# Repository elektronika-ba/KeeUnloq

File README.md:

# KeeUnloq
Tool for playing with Microchip KeeLoq technology.

# Status
Under development. More information will be available on www.elektronika.ba

Read the doc @ [Documentation](doc/KeeUnloq_fw1.0.docx)

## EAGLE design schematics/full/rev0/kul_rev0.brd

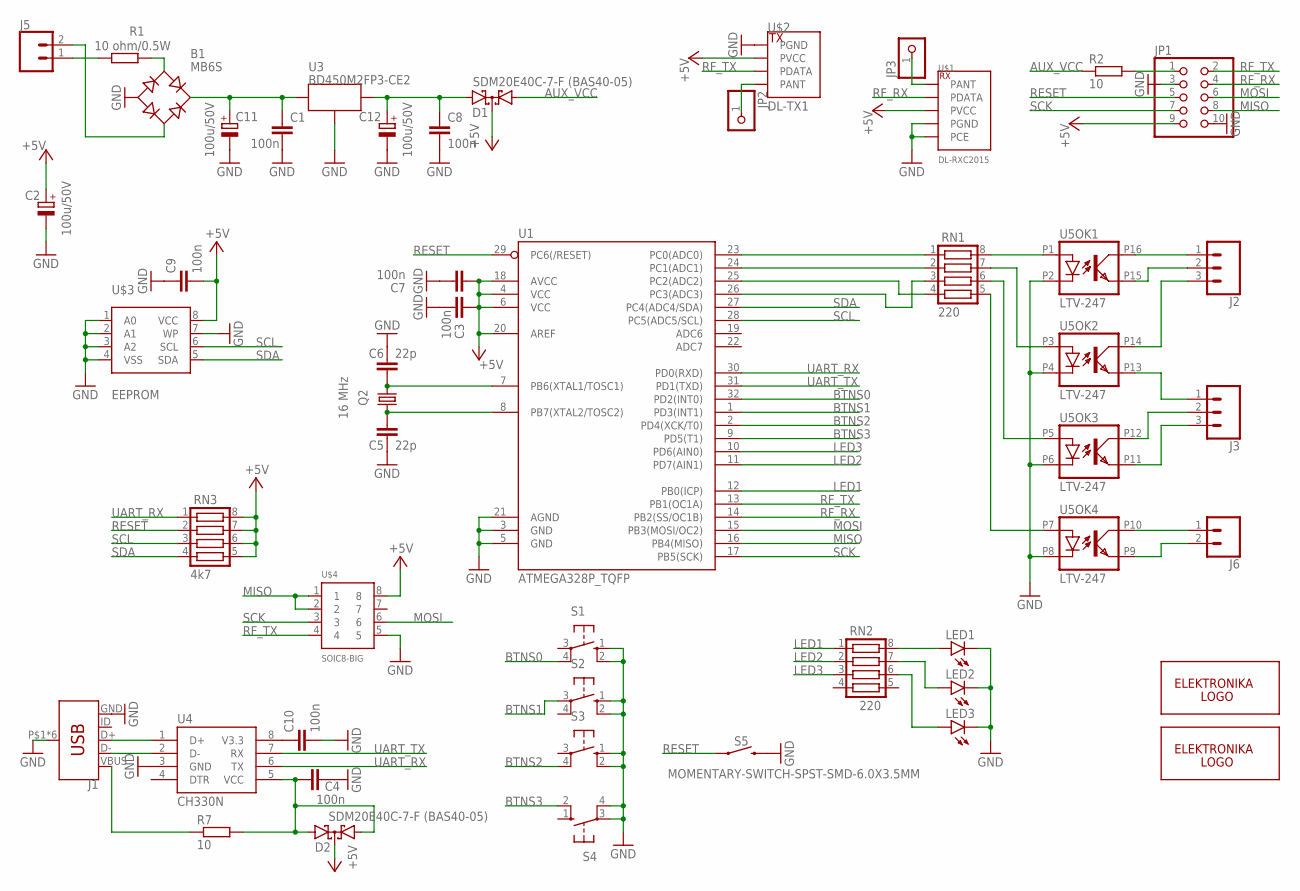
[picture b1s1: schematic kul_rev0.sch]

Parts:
B1: MB6S; SOIC-4
C1, C3, C4, C7, C8, C9, C10: 100n; C0603
C2, C11, C12: 100u/50V; E5-6
C5, C6: 22p; C0603
D1, D2: SDM20E40C-7-F (BAS40-05); SOT23
J1: USB_MICRO-BLCSC; C40951_USB
J2, J3: CONN_03SCREW_LOCK; SCREWTERMINAL-3.5MM-3_LOCK.007S
J5, J6: CONN_023.5MM; SCREWTERMINAL-3.5MM-2
JP1: PINHD-2X5; 2X05
JP2, JP3: PINHD-1X1; 1X01
LED1, LED2, LED3: LEDCHIP-LED0805; CHIP-LED0805
Q2: 16 MHz; 3.2X2.5_KX-7
R1: 10 ohm/0.5W; R0805
R2, R7: 10; R0603
RN1, RN2: 220; CTS742C083
RN3: 4k7; CTS742C083
S1, S2, S3, S4: 10-XX; B3F-10XX
S5: MOMENTARY-SWITCH-SPST-SMD-6.0X3.5MM; TACTILE_SWITCH_SMD_6.0X3.5MM
U1: ATMEGA328P_TQFP; TQFP32-08
U3: BD450M2FP3-CE2; C308597_LDO
U4: CH330N; SOIC8
U5: LTV-247; SOP-16_4.4MM
U$1: DL-RXC2015
U$2: DL-TX1
U$3: EEPROM; SOIC8
U$4: SOIC8-BIG; SOIC8_BIG
U$5: ELEKTRONIKA_BA_ELEBA_LOGO-121; ELEKTRONIKA_BA_ELEBALOGO_ELEBALOGO_B_121
U$6: ELEKTRONIKA_BA_ELEBA_LOGO; ELEKTRONIKA_BA_ELEBALOGO_ELEBALOGO_B_122

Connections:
+5V: C2.+, C3.2, C7.2, C9.2, D1.3 (C), D2.3 (C), JP1.9, RN3.5, RN3.6, RN3.7, RN3.8, U1.4 (VCC), U1.6 (VCC), U1.18 (AVCC), U1.20 (AREF), U$1.PVCC, U$2.PVDD (PVCC), U$3.8 (VCC), U$4.8
AUX_VCC: D1.1 (A1), R2.1
BTNS0: S1.4 (P1), U1.32 (PD2(INT0))
BTNS1: S2.3, U1.1 (PD3(INT1))
BTNS2: S3.4 (P1), U1.2 (PD4(XCK/T0))
BTNS3: S4.2 (S1), U1.9 (PD5(T1))
GND: B1.-, C1.2, C2.-, C3.1, C4.2, C5.2, C6.1, C7.1, C8.2, C9.1, C10.2, C11.-, C12.-, J1.GND, J1.P$1 (SHIELD), J1.P$2 (SHIELD), J1.P$3 (SHIELD), J1.P$4 (SHIELD), J1.SHIELD1 (SHIELD), J1.SHIELD2 (SHIELD), JP1.3, JP1.10, LED1.C, LED2.C, LED3.C, S1.1 (S), S1.2 (S1), S2.1 (S), S2.2 (S1), S3.1 (S), S3.2 (S1), S4.3, S4.4 (P1), S5.2, U1.3 (GND), U1.5 (GND), U1.21 (AGND), U3.PGND1 (PGND), U3.PGND2 (PGND), U4.3 (GND), U5.P2 (C), U5.P4 (C), U5.P6 (C), U5.P8 (C), U$1.PCE, U$1.PGND1 (PGND), U$1.PGND2 (PGND), U$2.PGND, U$3.1 (A0), U$3.2 (A1), U$3.3 (A2), U$3.4 (VSS), U$3.7 (WP), U$4.5
LED1: RN2.1, U1.12 (PB0(ICP))
LED2: RN2.2, U1.11 (PD7(AIN1))
LED3: RN2.3, U1.10 (PD6(AIN0))
MISO: JP1.8, U1.16 (PB4(MISO)), U$4.1, U$4.2
MOSI: JP1.6, U1.15 (PB3(MOSI/OC2)), U$4.6
unnamed: RN1.8, U5.P1 (A)
unnamed: RN1.7, U5.P3 (A)
unnamed: RN1.6, U5.P5 (A)
unnamed: RN1.5, U5.P7 (A)
unnamed: RN1.4, U1.25 (PC2(ADC2))
unnamed: RN1.3, U1.26 (PC3(ADC3))
unnamed: J1.D+, U4.1 (D+)
unnamed: B1.~1 (AC1), R1.1
unnamed: B1.~2 (AC2), J5.2
unnamed: B1.+, C1.1, C11.+, U3.PIN
unnamed: C8.1, C12.+, D1.2 (A2), U3.POUT
unnamed: J5.1, R1.2
unnamed: J1.D-, U4.2 (D-)
unnamed: J1.VBUS, R7.1
unnamed: C4.1, D2.1 (A1), D2.2 (A2), R7.2, U4.5 (VCC)
unnamed: C10.1, U4.8 (V3.3)
unnamed: J2.1, U5.P16 (COL)
unnamed: J2.2, U5.P15 (EMIT)
unnamed: J2.3, U5.P14 (COL)
unnamed: J3.1, U5.P13 (EMIT)
unnamed: J3.2, U5.P12 (COL)
unnamed: J3.3, U5.P11 (EMIT)
unnamed: J6.1, U5.P10 (COL)
unnamed: J6.2, U5.P9 (EMIT)
unnamed: RN1.1, U1.23 (PC0(ADC0))
unnamed: RN1.2, U1.24 (PC1(ADC1))
unnamed: JP2.1, U$2.PANT
unnamed: JP3.1, U$1.PANT
unnamed: LED1.A, RN2.8
unnamed: LED2.A, RN2.7
unnamed: LED3.A, RN2.6
unnamed: JP1.1, R2.2
OSC1: C6.2, Q2.3 (2), U1.7 (PB6(XTAL1/TOSC1))
OSC2: C5.1, Q2.1, U1.8 (PB7(XTAL2/TOSC2))
RESET: JP1.5, RN3.2, S5.1, U1.29 (PC6(/RESET))
RF_RX: JP1.4, U1.14 (PB2(SS/OC1B)), U$1.PDATA
RF_TX: JP1.2, U1.13 (PB1(OC1A)), U$2.PDATA, U$4.4
SCK: JP1.7, U1.17 (PB5(SCK)), U$4.3
SCL: RN3.3, U1.28 (PC5(ADC5/SCL)), U$3.6 (SCL)
SDA: RN3.4, U1.27 (PC4(ADC4/SDA)), U$3.5 (SDA)
UART_RX: RN3.1, U1.30 (PD0(RXD)), U4.6 (TX)
UART_TX: U1.31 (PD1(TXD)), U4.7 (RX)

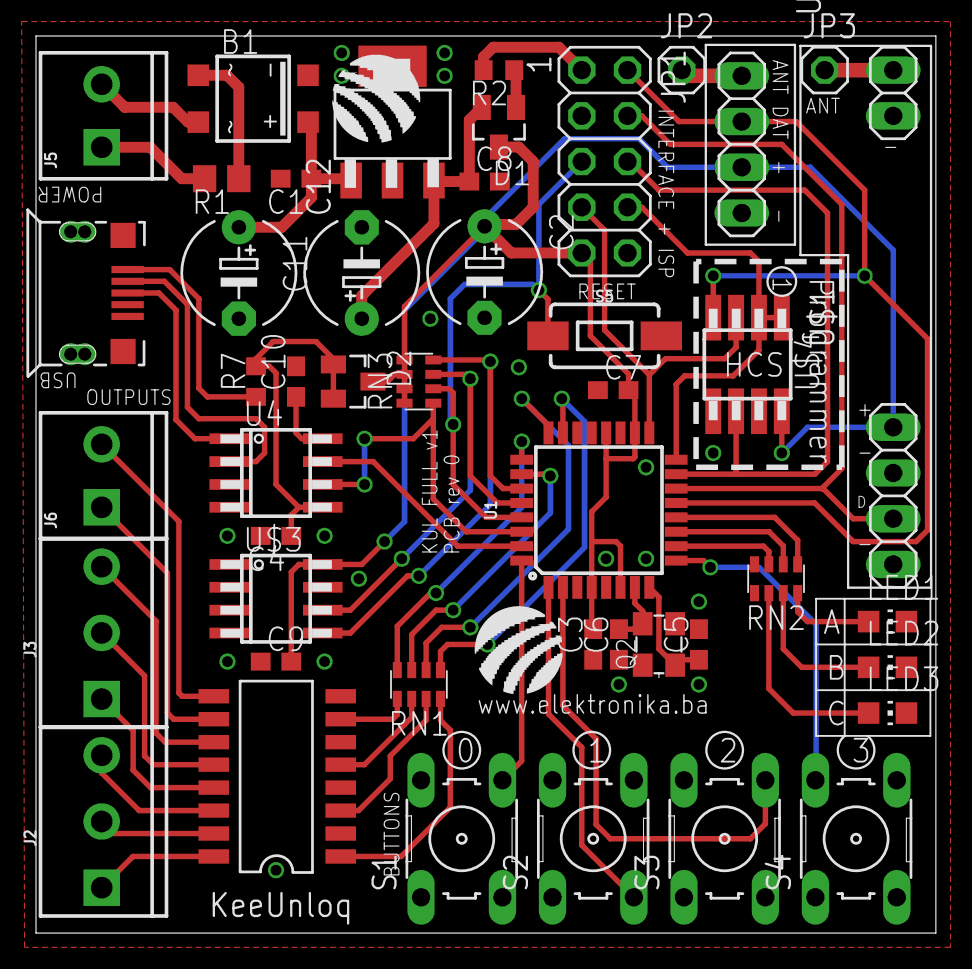
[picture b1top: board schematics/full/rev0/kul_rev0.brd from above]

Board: 2 copper layers, 50.0 x 49.8 mm, 48 parts (1 on the bottom side), 54 nets.

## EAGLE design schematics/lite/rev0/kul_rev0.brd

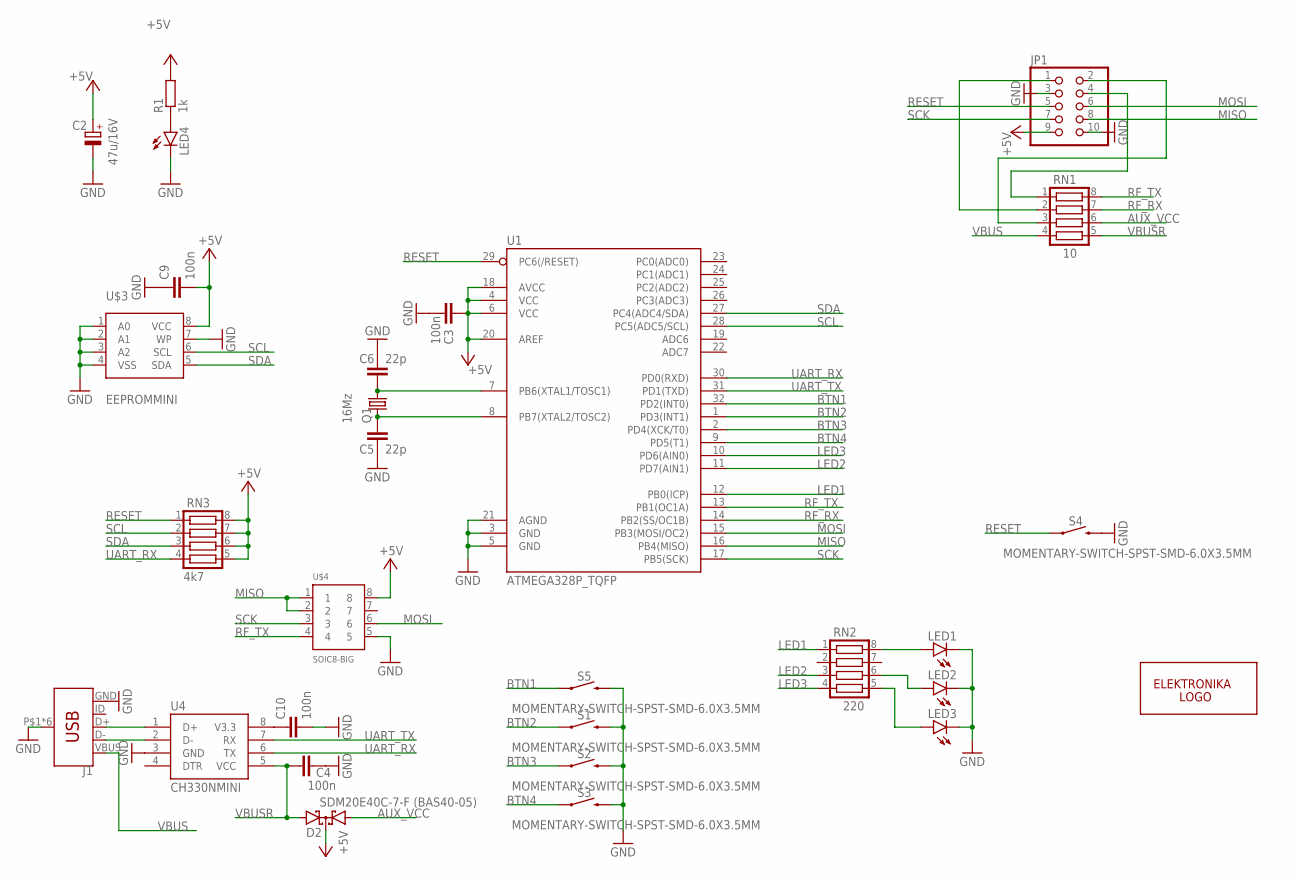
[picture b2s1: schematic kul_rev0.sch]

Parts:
C2: 47u/16V; CT6032
C3, C4, C9, C10: 100n; C0603
C5, C6: 22p; C0603
D2: SDM20E40C-7-F (BAS40-05); SOT23
J1: USB_MICRO-BLCSC; C40951_USB
JP1: PINHD-2X5/90; 2X05/90
LED1, LED2, LED3, LED4: LEDCHIP-LED0805; CHIP-LED0805
Q1: 16Mz; 3.2X2.5_KX-7
R1: 1k; R0603
RN1: 10; CTS742C083
RN2: 220; CTS742C083
RN3: 4k7; CTS742C083
S1, S2, S3, S4, S5: MOMENTARY-SWITCH-SPST-SMD-6.0X3.5MM; TACTILE_SWITCH_SMD_6.0X3.5MM
U1: ATMEGA328P_TQFP; TQFP32-08
U4: CH330NMINI; SOIC8_MINI
U$3: EEPROMMINI; SOIC8_MINI
U$4: SOIC8-BIG; SOIC8_BIG
U$6: ELEKTRONIKA_BA_ELEBA_LOGO; ELEKTRONIKA_BA_ELEBALOGO_ELEBALOGO_B_122

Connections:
+5V: C2.+, C3.2, C9.2, D2.3 (C), JP1.9, R1.2, RN3.5, RN3.6, RN3.7, RN3.8, U1.4 (VCC), U1.6 (VCC), U1.18 (AVCC), U1.20 (AREF), U$3.8 (VCC), U$4.8
AUX_VCC: D2.1 (A1), RN1.6
BTN1: S5.1, U1.32 (PD2(INT0))
BTN2: S1.1, U1.1 (PD3(INT1))
BTN3: S2.1, U1.2 (PD4(XCK/T0))
BTN4: S3.1, U1.9 (PD5(T1))
GND: C2.-, C3.1, C4.2, C5.2, C6.1, C9.1, C10.2, J1.GND, J1.P$1 (SHIELD), J1.P$2 (SHIELD), J1.P$3 (SHIELD), J1.P$4 (SHIELD), J1.SHIELD1 (SHIELD), J1.SHIELD2 (SHIELD), JP1.3, JP1.10, LED1.C, LED2.C, LED3.C, LED4.C, S1.2, S2.2, S3.2, S4.2, S5.2, U1.3 (GND), U1.5 (GND), U1.21 (AGND), U4.3 (GND), U$3.1 (A0), U$3.2 (A1), U$3.3 (A2), U$3.4 (VSS), U$3.7 (WP), U$4.5
LED1: RN2.1, U1.12 (PB0(ICP))
LED2: RN2.3, U1.11 (PD7(AIN1))
LED3: RN2.4, U1.10 (PD6(AIN0))
MISO: JP1.8, U1.16 (PB4(MISO)), U$4.1, U$4.2
MOSI: JP1.6, U1.15 (PB3(MOSI/OC2)), U$4.6
unnamed: JP1.2, RN1.3
unnamed: JP1.4, RN1.1
unnamed: LED2.A, RN2.6
unnamed: LED1.A, RN2.8
unnamed: LED4.A, R1.1
unnamed: J1.D+, U4.1 (D+)
unnamed: J1.D-, U4.2 (D-)
unnamed: C10.1, U4.8 (V3.3)
unnamed: LED3.A, RN2.5
unnamed: JP1.1, RN1.2
OSC1: C6.2, Q1.3 (2), U1.7 (PB6(XTAL1/TOSC1))
OSC2: C5.1, Q1.1, U1.8 (PB7(XTAL2/TOSC2))
RESET: JP1.5, RN3.1, S4.1, U1.29 (PC6(/RESET))
RF_RX: RN1.7, U1.14 (PB2(SS/OC1B))
RF_TX: RN1.8, U1.13 (PB1(OC1A)), U$4.4
SCK: JP1.7, U1.17 (PB5(SCK)), U$4.3
SCL: RN3.2, U1.28 (PC5(ADC5/SCL)), U$3.6 (SCL)
SDA: RN3.3, U1.27 (PC4(ADC4/SDA)), U$3.5 (SDA)
UART_RX: RN3.4, U1.30 (PD0(RXD)), U4.6 (TX)
UART_TX: U1.31 (PD1(TXD)), U4.7 (RX)
VBUS: J1.VBUS, RN1.4
VBUSR: C4.1, D2.2 (A2), RN1.5, U4.5 (VCC)

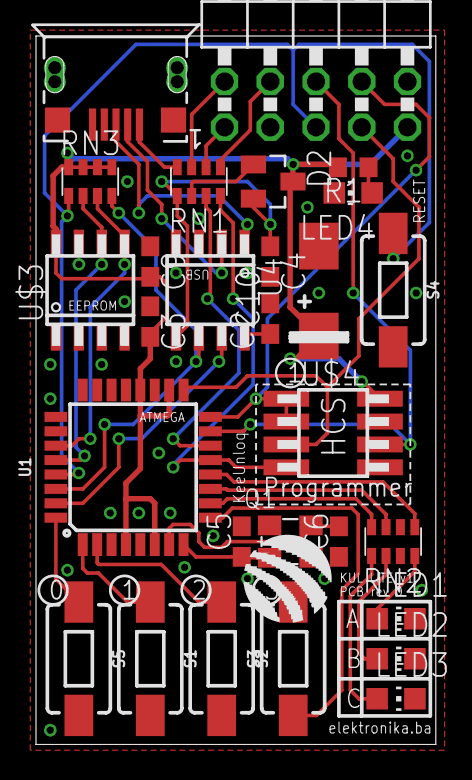
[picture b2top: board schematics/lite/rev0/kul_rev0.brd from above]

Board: 2 copper layers, 22.2 x 39.4 mm, 29 parts (1 on the bottom side), 34 nets.

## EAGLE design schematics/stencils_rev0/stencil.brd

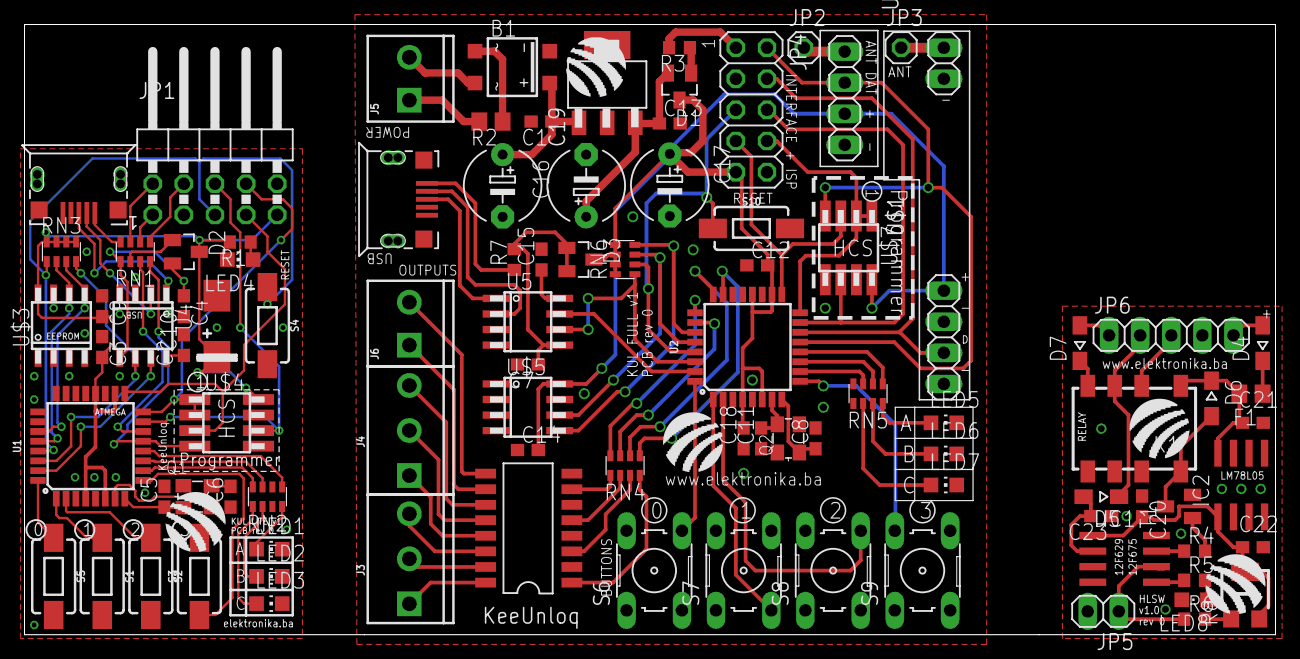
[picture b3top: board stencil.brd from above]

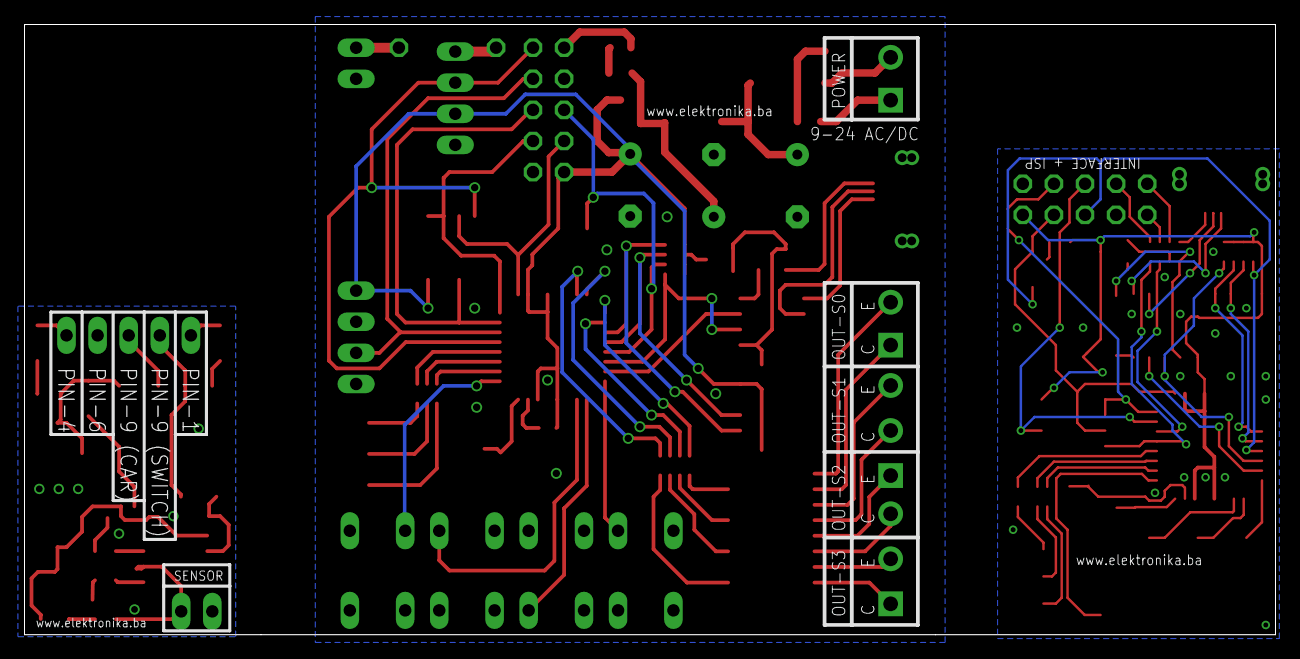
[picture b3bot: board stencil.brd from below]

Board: 2 copper layers, 102.2 x 49.8 mm, 99 parts (3 on the bottom side), 105 nets.

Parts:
B1: MB6S; SOIC-4
C1, C3, C4, C7, C9, C10, C12, C13, C14, C15, C18, C20, C23: 100n; C0603
C2: 47u/16V; CT6032
C5, C6, C8, C11: 22p; C0603
C16, C17, C19: 100u/50V; E5-6
C21: 470n; C0603
C22: 330n; C0603
D1, D2, D3: SDM20E40C-7-F (BAS40-05); SOT23
D4, D5, D6, D7: 1N4148; SOD323-W
F1: PTC 0.1A 15V; R0805
IC1: PIC12F675SN; SO-08
IC2: 78L05SMD; SO08
J1, J2: C40951_USB
J3, J4: SCREWTERMINAL-3.5MM-3_LOCK.007S
J5, J6: SCREWTERMINAL-3.5MM-2
JP1: 2X05/90
JP2, JP3: 1X01
JP4: 2X05
JP5: 1X02
JP6: 1X05
K1: G6K-2F-Y
LED1, LED2, LED3, LED4, LED5, LED6, LED7: CHIP-LED0805
LED8: RED; CHIPLED_0805
Q1: 16Mz; 3.2X2.5_KX-7
Q2: 16 MHz; 3.2X2.5_KX-7
R1, R5, R6: 1k; R0603
R2: 22; R0805
R3, R7: 10; R0603
R4: 2k2; R0603
R8: 15k; RTRIMCVR42A
RN1: 10; CTS742C083
RN2, RN4, RN5: 220; CTS742C083
RN3, RN6: 4k7; CTS742C083
S1, S2, S3, S4, S5, S10: MOMENTARY-SWITCH-SPST-SMD-6.0X3.5MM; TACTILE_SWITCH_SMD_6.0X3.5MM
S6, S7, S8, S9: B3F-10XX
T1: BC546; SOT23-BEC
U1, U2: ATMEGA328P_TQFP; TQFP32-08
U3: BD450M2FP3-CE2; C308597_LDO
U4: CH330NMINI; SOIC8_MINI
U5: CH330N; SOIC8
U6: LTV-247; SOP-16_4.4MM
U$1: DL-RXC2015
U$2: DL-TX1
U$3: EEPROMMINI; SOIC8_MINI
U$4, U$7: SOIC8-BIG; SOIC8_BIG
U$5: EEPROM; SOIC8
U$6, U$9, U$10: ELEKTRONIKA_BA_ELEBA_LOGO; ELEKTRONIKA_BA_ELEBALOGO_ELEBALOGO_B_122
U$8, U$11: ELEKTRONIKA_BA_ELEBA_LOGO-121; ELEKTRONIKA_BA_ELEBALOGO_ELEBALOGO_B_121

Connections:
1-PIN: D7.A, JP6.1
4-PIN: D4.A, JP6.5
9-CAR: JP6.3, K1.2
9-HLSW: D5.C, JP6.2, K1.3
!ENAB: C23.2, D5.A, IC1.2
+5V: C2.+, C3.2, C9.2, D2.3, JP1.9, R1.2, RN3.5, RN3.6, RN3.7, RN3.8, U1.4, U1.6, U1.18, U1.20, U$3.8, U$4.8
+5V1: C12.2, C14.2, C17.+, C18.2, D1.3, D3.3, JP4.9, RN6.5, RN6.6, RN6.7, RN6.8, U2.4, U2.6, U2.18, U2.20, U$1.PVCC, U$2.PVDD, U$5.8, U$7.8
+5V2: C20.2, C22.1, IC1.1, IC2.1, R8.2, R8.3
+12V: C21.1, D6.C, F1.2, IC2.8, K1.1
AUX_VCC: D2.1, RN1.6
AUX_VCC1: D1.1, R3.1
BTN1: S5.1, U1.32
BTN2: S1.1, U1.1
BTN3: S2.1, U1.2
BTN4: S3.1, U1.9
BTN5: S6.4, U2.32
BTN6: S7.3, U2.1
BTN7: S8.4, U2.2
BTN8: S9.2, U2.9
GND: C2.-, C3.1, C4.2, C5.2, C6.1, C9.1, C10.2, J1.GND, J1.P$1, J1.P$2, J1.P$3, J1.P$4, J1.SHIELD1, J1.SHIELD2, JP1.3, JP1.10, LED1.C, LED2.C, LED3.C, LED4.C, S1.2, S2.2, S3.2, S4.2, S5.2, U1.3, U1.5, U1.21, U4.3, U$3.1, U$3.2, U$3.3, U$3.4, U$3.7, U$4.5
GND1: B1.-, C1.2, C7.2, C8.2, C11.1, C12.1, C13.2, C14.1, C15.2, C16.-, C17.-, C18.1, C19.-, J2.GND, J2.P$1, J2.P$2, J2.P$3, J2.P$4, J2.SHIELD1, J2.SHIELD2, JP4.3, JP4.10, LED5.C, LED6.C, LED7.C, S6.1, S6.2, S7.1, S7.2, S8.1, S8.2, S9.3, S9.4, S10.2, U2.3, U2.5, U2.21, U3.PGND1, U3.PGND2, U5.3, U6.P2, U6.P4, U6.P6, U6.P8, U$1.PCE, U$1.PGND1, U$1.PGND2, U$2.PGND, U$5.1, U$5.2, U$5.3, U$5.4, U$5.7, U$7.5
GND2: C20.1, C21.2, C22.2, C23.1, IC1.8, IC2.2, IC2.3, IC2.6, IC2.7, JP5.2, JP6.4, LED8.C, T1.E
LED1: RN2.1, U1.12
LED2: RN2.3, U1.11
LED3: RN2.4, U1.10
LED4: RN5.1, U2.12
LED5: RN5.2, U2.11
LED6: RN5.3, U2.10
MISO: JP1.8, U1.16, U$4.1, U$4.2
MISO1: JP4.8, U2.16, U$7.1, U$7.2
MOSI: JP1.6, U1.15, U$4.6
MOSI1: JP4.6, U2.15, U$7.6
unnamed: JP1.2, RN1.3
unnamed: JP1.4, RN1.1
unnamed: LED2.A, RN2.6
unnamed: LED1.A, RN2.8
unnamed: LED4.A, R1.1
unnamed: RN4.8, U6.P1
unnamed: RN4.7, U6.P3
unnamed: J1.D+, U4.1
unnamed: RN4.6, U6.P5
unnamed: RN4.5, U6.P7
unnamed: B1.~1, R2.1
unnamed: B1.~2, J5.2
unnamed: B1.+, C1.1, C16.+, U3.PIN
unnamed: J1.D-, U4.2
unnamed: C13.1, C19.+, D1.2, U3.POUT
unnamed: J2.D+, U5.1
unnamed: C10.1, U4.8
unnamed: J2.D-, U5.2
unnamed: J2.VBUS, R7.1
unnamed: C7.1, D3.1, D3.2, R7.2, U5.5
unnamed: C15.1, U5.8
unnamed: J3.1, U6.P16
unnamed: J3.2, U6.P15
unnamed: J3.3, U6.P14
unnamed: J4.1, U6.P13
unnamed: J4.2, U6.P12
unnamed: J4.3, U6.P11
unnamed: J6.1, U6.P10
unnamed: J6.2, U6.P9
unnamed: RN4.1, U2.23
unnamed: RN4.2, U2.24
unnamed: JP2.1, U$2.PANT
unnamed: JP3.1, U$1.PANT
unnamed: LED3.A, RN2.5
unnamed: JP1.1, RN1.2
unnamed: LED5.A, RN5.8
unnamed: LED6.A, RN5.7
unnamed: LED7.A, RN5.6
unnamed: J5.1, R2.2
unnamed: JP4.1, R3.2
unnamed: RN4.4, U2.25
unnamed: RN4.3, U2.26
unnamed: D4.C, F1.1
unnamed: LED8.A, R5.2
unnamed: IC1.6, JP5.1, R6.1
unnamed: IC1.5, R5.1
unnamed: R4.2, T1.B
unnamed: IC1.7, R4.1
unnamed: D6.A, K1.8, T1.C
unnamed: D7.C, K1.4
unnamed: R6.2, R8.1
OSC1: C6.2, Q1.3, U1.7
OSC2: C5.1, Q1.1, U1.8
OSC3: C11.2, Q2.3, U2.7
OSC4: C8.1, Q2.1, U2.8
RESET: JP1.5, RN3.1, S4.1, U1.29
RESET1: JP4.5, RN6.2, S10.1, U2.29
RF_RX: RN1.7, U1.14
RF_RX1: JP4.4, U2.14, U$1.PDATA
RF_TX: RN1.8, U1.13, U$4.4
RF_TX1: JP4.2, U2.13, U$2.PDATA, U$7.4
SCK: JP1.7, U1.17, U$4.3
SCK1: JP4.7, U2.17, U$7.3
SCL: RN3.2, U1.28, U$3.6
SCL1: RN6.3, U2.28, U$5.6
SDA: RN3.3, U1.27, U$3.5
SDA1: RN6.4, U2.27, U$5.5
UART_RX: RN3.4, U1.30, U4.6
UART_RX1: RN6.1, U2.30, U5.6
UART_TX: U1.31, U4.7
UART_TX1: U2.31, U5.7
VBUS: J1.VBUS, RN1.4
VBUSR: C4.1, D2.2, RN1.5, U4.5

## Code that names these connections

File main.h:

/*
 * main.h
 *
 * Created: 26. 1. 2021. 09:56:45
 *  Author: Trax
 */

#ifndef MAIN_H_
#define MAIN_H_

#include "lib/uart/uart.h"
#include "lib/i2c/i2c.h"

#include "keeloq.h"
#include "keeloq_decode.h"
#include "keeloq_prog.h"
#include "ee_db.h"
#include "ee_db_record.h"

#define DEBUG 1

// Limitations: ATmega328P (and family) PORTB.4 can only be used as INPUT if SPI mode is enabled.

#ifndef F_CPU
	#error You must define CPU frequency (F_CPU) in AVR Studio (Project Properties -> Toolchain -> Symbols >> add F_CPU=16000000UL) or your Makefile
#endif

#ifndef _BV
	#define _BV(n) (1 << n)
#endif

#define	calc_UBRR(bau)			(F_CPU/16/bau-1)
#define calc_TWI(khz)			(((F_CPU/khz) - 16)/2)

#define nop() asm volatile("nop")

// EEPROM addresses
#define	EEPROM_START				(0)								// start of our data in eeprom is here
#define EEPROM_MAGIC				(EEPROM_START + 0)				// eeprom OK - magic value
#define EEPROM_OPTION_STATES		(EEPROM_MAGIC + 1)				// state of operating options
#define EEPROM_MASTER_CRYPT_KEY		(EEPROM_OPTION_STATES + 1)		// master crypt key for learning encrypted HCS devices via RF

#define EEPROM_MAGIC_VALUE			0xAA

// Device options state
#define OP_STATE_1		0b00000001	// Receiver module
#define OP_STATE_2		0b00000010	// MITM upgrader
#define OP_STATE_3		0b00000100	// Grab, collect
#define OP_STATE_4		0b00001000	// Remote emulator from memory
#define OP_STATE_LEN	4			// 4 options currently implemented

// RF IN data pin
#define	RX_PIN			2
#define	RX_DDR			DDRB
#define	RX_PINREG		PINB
#define	RX_PORT			PORTB
#define	RX_PCINTBIT		PCINT2
#define	RX_PCMSKREG		PCMSK0
#define	RX_PCICRBIT		PCIE0

// RF OUT data pin PORTB.1 (OC1A pin is data output)
#define	TX_PIN			1
#define	TX_DDR			DDRB
#define	TX_PORT			PORTB

// OPTOCOUPLERs outputs S0..S3
#define	S0_PIN			2
#define	S0_DDR			DDRC
#define	S0_PORT			PORTC

#define	S1_PIN			3
#define	S1_DDR			DDRC
#define	S1_PORT			PORTC

#define	S2_PIN			1
#define	S2_DDR			DDRC
#define	S2_PORT			PORTC

#define	S3_PIN			0
#define	S3_DDR			DDRC
#define	S3_PORT			PORTC

// BUTTONs inputs
#define	BTNS0_PIN			2
#define	BTNS0_DDR			DDRD
#define	BTNS0_PINREG		PIND
#define	BTNS0_PORT			PORTD
#define	BTNS0_PCINTBIT		PCINT18
#define	BTNS0_PCMSKREG		PCMSK2
#define	BTNS0_PCICRBIT		PCIE2

#define	BTNS1_PIN			3
#define	BTNS1_DDR			DDRD
#define	BTNS1_PINREG		PIND
#define	BTNS1_PORT			PORTD
#define	BTNS1_PCINTBIT		PCINT19
#define	BTNS1_PCMSKREG		PCMSK2
#define	BTNS1_PCICRBIT		PCIE2

#define	BTNS2_PIN			4
#define	BTNS2_DDR			DDRD
#define	BTNS2_PINREG		PIND
#define	BTNS2_PORT			PORTD
#define	BTNS2_PCINTBIT		PCINT20
#define	BTNS2_PCMSKREG		PCMSK2
#define	BTNS2_PCICRBIT		PCIE2

#define	BTNS3_PIN			5
#define	BTNS3_DDR			DDRD
#define	BTNS3_PINREG		PIND
#define	BTNS3_PORT			PORTD
#define	BTNS3_PCINTBIT		PCINT21
#define	BTNS3_PCMSKREG		PCMSK2
#define	BTNS3_PCICRBIT		PCIE2

// for prev_btn & btn_hold global variables
#define BTNS0_MASK			0b00000001
#define BTNS1_MASK			0b00000010
#define BTNS2_MASK			0b00000100
#define BTNS3_MASK			0b00001000

// Button related timers
#define	BTN_HOLD_TMR						950		// miliseconds to pronounce button as held rather than pressed
#define BTN_MODE_CHANGE_EXPECTER			15000	// ms to exit the mode-change.. mode
#define BTN_MODE_CHANGE_CURR_REPORTER		2000	// ms, on every this much report current mode of operation
#define BTN_PROG_N_ENROLL_EXPECTER			20000	// ms to expect button press for programming the encoder IC
#define BTN_REMOVE_REMOTE_EXPECTER			10000	// ms to expect remote reception via RF and to remove it
#define BTN_ENROLL_FIRST_REMOTE_EXPECTER	10000	// ms to expect FIRST remote reception via RF and to enroll it
#define BTN_ENROLL_SECOND_REMOTE_EXPECTER	5000	// ms to expect SECOND remote reception via RF and to enroll it
#define BTN_CLEAR_MEMORY_EXPECTER			5000	// ms to expect second button hold for entire memory to be cleared

// LEDs
#define	LEDA_PIN		0
#define	LEDA_DDR		DDRB
#define	LEDA_PORT		PORTB

#define	LEDB_PIN		7
#define	LEDB_DDR		DDRD
#define	LEDB_PORT		PORTD

#define	LEDC_PIN		6
#define	LEDC_DDR		DDRD
#define	LEDC_PORT		PORTD

// HCS PROGRAMMER PINS
// DATA
#define	HCS_PROG_DATA_PIN		3
#define	HCS_PROG_DATA_DDR		DDRB
#define	HCS_PROG_DATA_PINREG	PINB
#define	HCS_PROG_DATA_PORT		PORTB
// S0&S1 pins
#define	HCS_PROG_S0S1_PIN		4
#define	HCS_PROG_S0S1_DDR		DDRB
#define	HCS_PROG_S0S1_PINREG	PINB
#define	HCS_PROG_S0S1_PORT		PORTB
// S2/CLK pin
#define	HCS_PROG_S2CLK_PIN		5
#define	HCS_PROG_S2CLK_DDR		DDRB
#define	HCS_PROG_S2CLK_PINREG	PINB
#define	HCS_PROG_S2CLK_PORT		PORTB
// S3 pin
#define	HCS_PROG_S3_PIN			1
#define	HCS_PROG_S3_DDR			DDRB
#define	HCS_PROG_S3_PINREG		PINB
#define	HCS_PROG_S3_PORT		PORTB

// Code macros
#define setInput(ddr, pin)		( (ddr) &= (uint8_t)~_BV(pin) )
#define setOutput(ddr, pin)		( (ddr) |= (uint8_t)_BV(pin) )

#define set0(port, pin)			( (port) &= (uint8_t)~_BV(pin) )
#define setLow(port, pin)		( (port) &= (uint8_t)~_BV(pin) )

#define set1(port, pin)			( (port) |= (uint8_t)_BV(pin) )
#define setHigh(port, pin)		( (port) |= (uint8_t)_BV(pin) )

#define togglePin(port, pin)	( (port) ^= (uint8_t)_BV(pin) )

// Boolean macros
#define	BSYS					0										// bank index[0] name.. used for system work
#define	BAPP1					1										// bank index[1] name.. used for application work
#define BOOL_BANK_SIZE			2										// how many banks (bytes)
#define bv(bit,bank) 			( bools[bank] & (uint8_t)_BV(bit) ) 	// boolean values GET/READ macro: if(bv(3,BSYS))...
#define	bs(bit,bank) 			( bools[bank] |= (uint8_t)_BV(bit) ) 	// boolean values SET macro: bs(5,BSYS)
#define	bc(bit,bank) 			( bools[bank] &= (uint8_t)~_BV(bit) ) 	// boolean values CLEAR macro: bc(4,BAPP1)
#define	bt(bit,bank) 			( bools[bank] ^= (uint8_t)_BV(bit) ) 	// boolean values TOGGLE macro: bt(6,BAPP1)

// Custom boolean bit/flags, 0..7 in bank 1 - SYSTEM SPECIFIC
#define	bUART_RX				0	// received byte is valid (1) or not (0)

// masks for the ISR LED blinker
#define ISR_LED_A_MASK			0b00000001
#define ISR_LED_B_MASK			0b00000010
#define ISR_LED_C_MASK			0b00000100

#define ISR_LED_BLINK_XFAST_MS	100
#define ISR_LED_BLINK_FAST_MS	150
#define ISR_LED_BLINK_NORMAL_MS	400
#define ISR_LED_BLINK_SLOW_MS	850

// misc stuff
uint8_t next_within_window(uint16_t, uint16_t, uint16_t);
void clear_pending_buttons();
uint8_t handle_ui_buttons();
void misc_hw_init();
void set_mode(uint8_t, uint8_t);
void update_settings_to_eeprom();
void delay_ms_(uint64_t);
void show_number_on_leds(uint16_t);
void handle_tx_emulator_buttons();
void delay_builtin_ms_(uint16_t);

uint8_t event_keydown(struct KEELOQ_DECODE_PLAIN *, struct eedb_record_header *, struct eedb_hcs_record *, uint8_t *);
void event_keyup(struct KEELOQ_DECODE_PLAIN *, struct eedb_record_header *, struct eedb_hcs_record *);

// LED helpers
void leda_on();
void leda_off();
void leda_blink(uint8_t);
void ledb_on();
void ledb_off();
void ledb_blink(uint8_t);
void ledc_on();
void ledc_off();
void ledc_blink(uint8_t);
void led_isrblink(uint8_t, uint16_t);

// main app stuff
uint8_t prog_n_enroll_66bit_hcs200(struct KEELOQ_DECODE_PROG_PROFILE *);
uint8_t prog_n_enroll_66bit_hcs201(struct KEELOQ_DECODE_PROG_PROFILE *);
uint8_t prog_n_enroll_66bit_hcs300_301_320(struct KEELOQ_DECODE_PROG_PROFILE *);
uint8_t prog_n_enroll_67bit_hcs360_361(struct KEELOQ_DECODE_PROG_PROFILE *);
uint8_t prog_hcs_encoder(struct KEELOQ_DECODE_PROG_PROFILE *);
void enroll_transmitter_rf();
void remove_transmitter_rf();
void clear_all_memory();

// hardware callbacks for keeloq library
void keeloq_rx_init_hw();
void keeloq_rx_deinit_hw();
void keeloq_init_tx_hw();
void keeloq_deinit_tx_hw();
void keeloq_pin_tx_hw(uint8_t);

// hardware callbacks for keeloq programmer library
void keeloq_prog_init_hw(uint8_t);
void keeloq_prog_set_clk_pin_hw(uint8_t);
void keeloq_prog_set_data_pin_hw(uint8_t);
uint8_t keeloq_prog_get_data_pin_hw();
void keeloq_prog_deinit_hw();

#endif /* MAIN_H_ */

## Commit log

2021-07-04 added doc folder
2021-07-04 added schematics
2021-07-05 fiddling
2021-07-08 not yet buildable
2021-07-12 under dev
2021-07-17 progress
2021-07-17 untested
2021-07-17 stuff working
2021-07-18 debugging TX emulator
2021-07-20 untested but tx might work
2022-06-17 #define biting my ass

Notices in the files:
parts and their libraries:
SparkFun-IC-Microcontroller: Licensing: Creative Commons ShareAlike 4.0 International - https://creativecommons.org/licenses/by-sa/4.0
crystal-geyer_V1_0: Copyright: Geyer-Electronic
